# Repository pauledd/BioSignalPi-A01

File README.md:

# BioSignalPi-A01

Eagle files for the BioSignalPi-A01 egc prototype.  
For application software look at http://martinr89.github.io/BiosignalPI  

Biosignal PI is licensed by Farhad Abtahi under a Creative Commons Attribution-NonCommercial-ShareAlike 4.0 International License. You are free to:  
    
    Share — copy and redistribute the material in any medium or format
    Adapt — remix, transform, and build upon the material

The licensor cannot revoke these freedoms as long as you follow the license terms.
Under the following terms:

Attribution — You must give appropriate credit, provide a link to the license, and indicate if changes were made. You may do so in any reasonable manner, but not in any way that suggests the licensor endorses you or your use.  
What does "Attribute this work" mean?  
The page you came from contained embedded licensing metadata, including how the creator wishes to be attributed for re-use. You can use the HTML here to cite the work. Doing so will also include metadata on your page so that others can find the original work as well.  

    NonCommercial — You may not use the material for commercial purposes.

    ShareAlike — If you remix, transform, or build upon the material, you must distribute your contributions under the same license as the original.

    No additional restrictions — You may not apply legal terms or technological measures that legally restrict others from doing anything the license permits.

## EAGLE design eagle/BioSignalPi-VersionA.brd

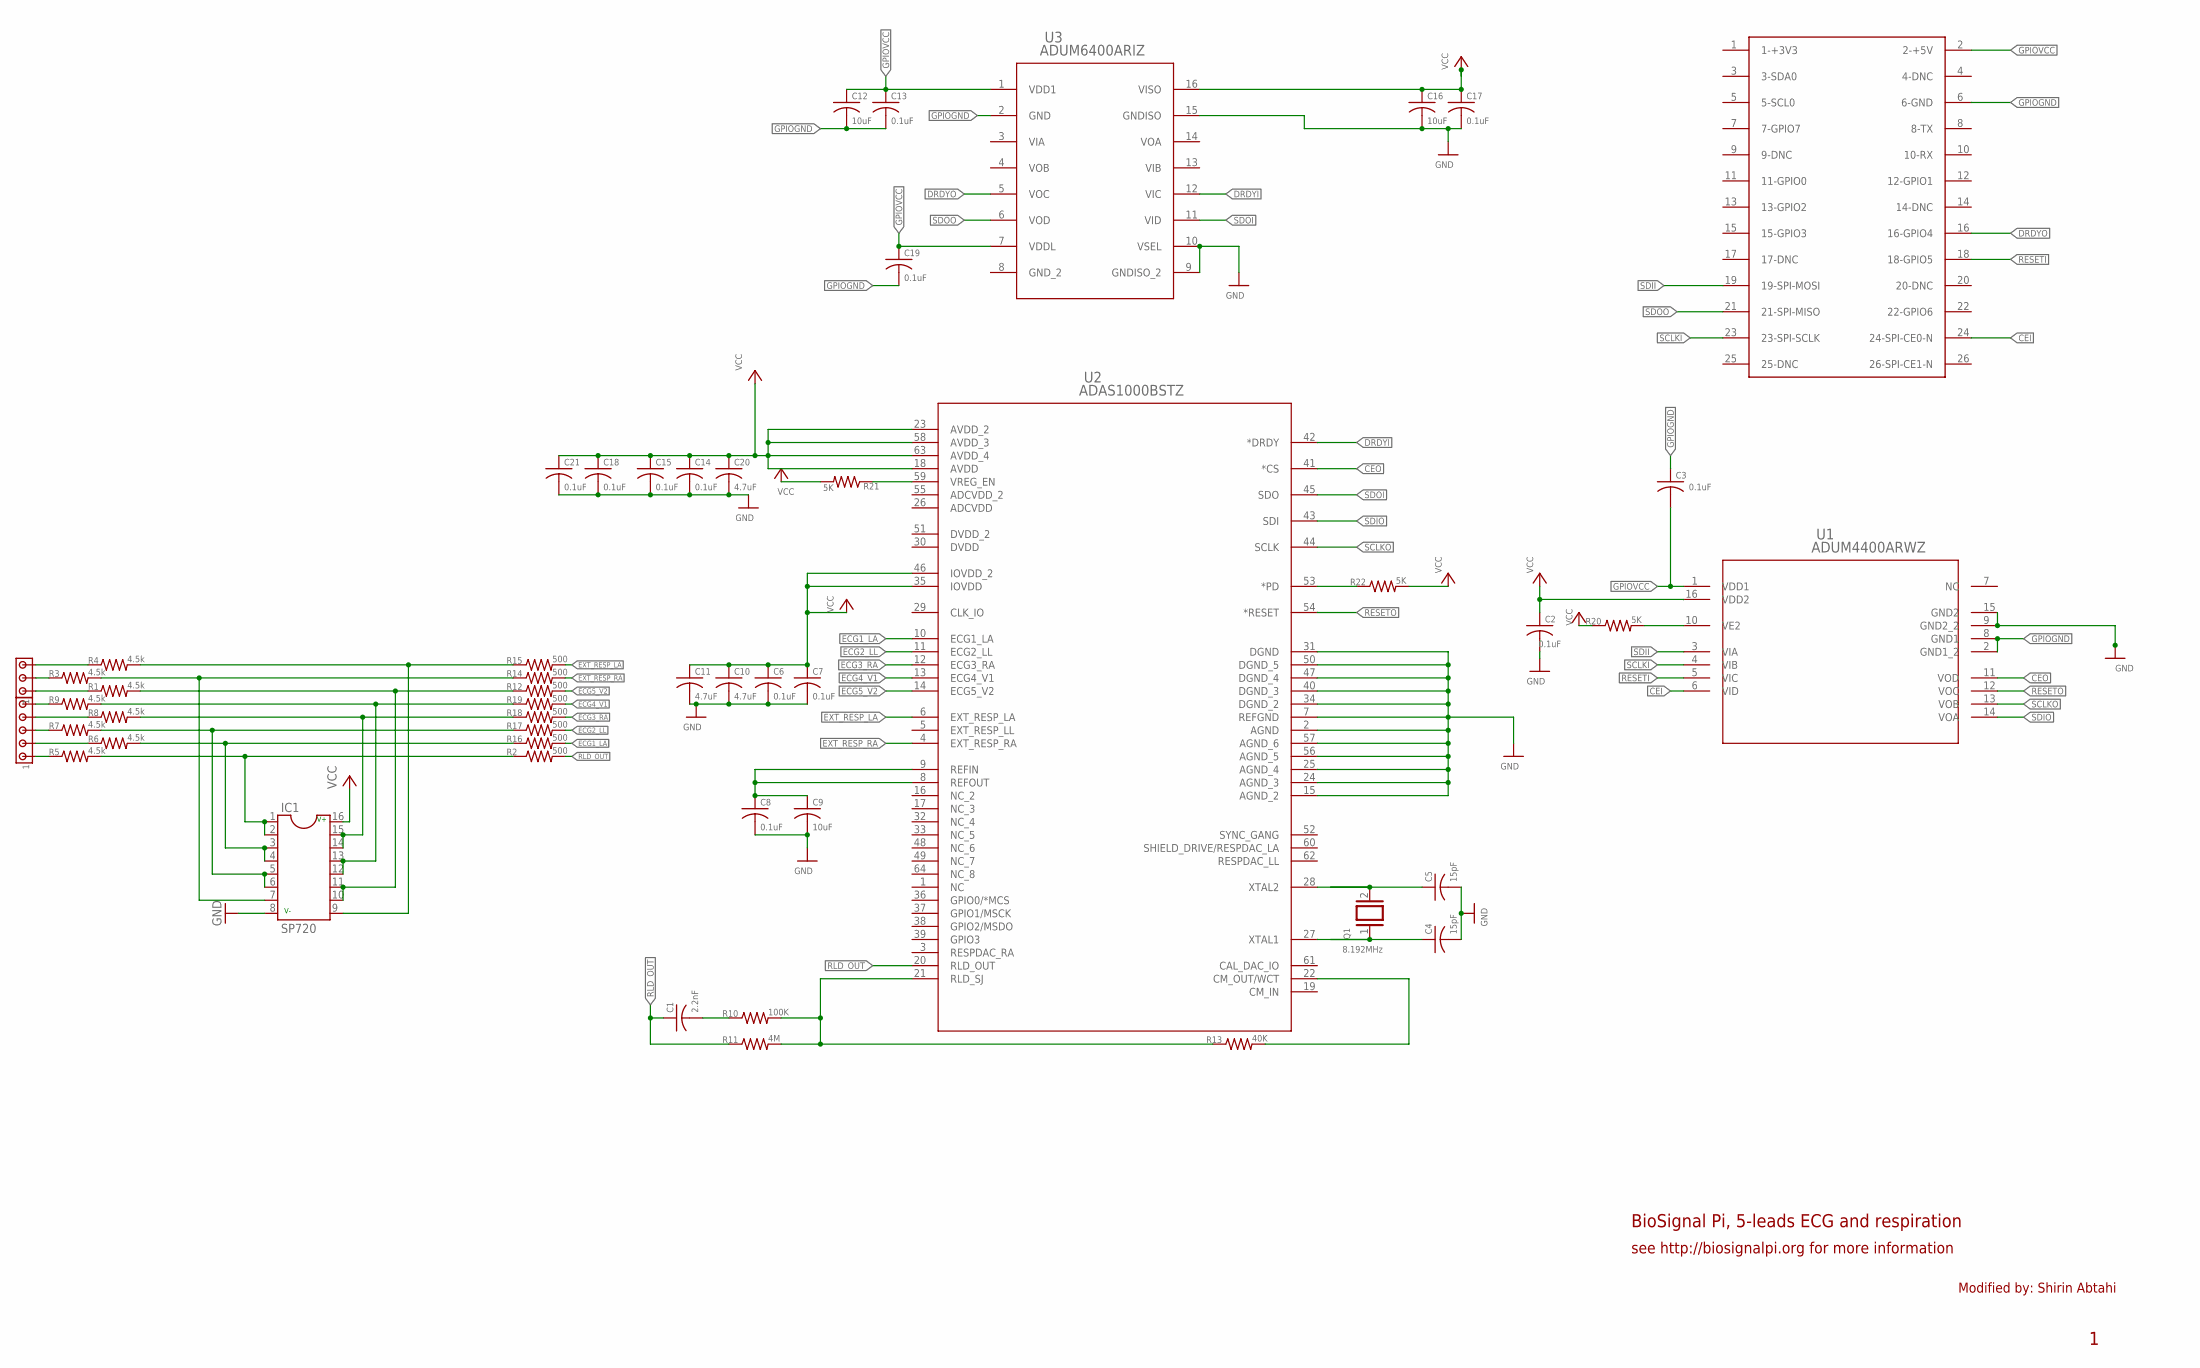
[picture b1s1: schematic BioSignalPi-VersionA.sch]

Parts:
C1: 2.2nF; C0805
C2, C3, C6, C7, C8, C13, C14, C15, C17, C18, C19, C21: 0.1uF; C0805
C4, C5: 15pF; C0805
C9, C12, C16: 10uF; C0805
C10, C11, C20: 4.7uF; C0805
IC1: SP720; DIL16
J1: JUMPERS; 10X03MTA
J2: JUMPERS; 10X05MTA
Q1: 8.192MHz; QS
R1, R3, R4, R5, R6, R7, R8, R9: 4.5k; R0805
R2, R12, R14, R15, R16, R17, R18, R19: 500; R0805
R10: 100K; R0805
R11: 4M; R0805
R13: 40K; R0805
R20, R21, R22: 5K; R0805
U1: ADUM4400ARWZ; RW_16
U2: ADAS1000BSTZ; ST_64_2
U3: ADUM6400ARIZ; RI_16_1
U$1: RASPBERRY-PI

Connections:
CEI: U1.6 (VID), U$1.24 (24-SPI-CE0-N)
CEO: U1.11 (VOD), U2.41 (*CS)
DRDYI: U2.42 (*DRDY), U3.12 (VIC)
DRDYO: U3.5 (VOC), U$1.16 (16-GPIO4)
ECG1_LA: R16.2, U2.10 (ECG1_LA)
ECG2_LL: R17.2, U2.11 (ECG2_LL)
ECG3_RA: R18.2, U2.12 (ECG3_RA)
ECG4_V1: R19.2, U2.13 (ECG4_V1)
ECG5_V2: R12.2, U2.14 (ECG5_V2)
EXT_RESP_LA: R15.2, U2.6 (EXT_RESP_LA)
EXT_RESP_RA: R14.2, U2.4 (EXT_RESP_RA)
GND: C2.2, C4.2, C5.2, C6.2, C7.2, C8.2, C9.2, C10.2, C11.2, C14.2, C15.2, C16.2, C17.2, C18.2, C20.2, C21.2, IC1.8, U1.9 (GND2_2), U1.15 (GND2), U2.2 (AGND), U2.7 (REFGND), U2.15 (AGND_2), U2.24 (AGND_3), U2.25 (AGND_4), U2.31 (DGND), U2.34 (DGND_2), U2.40 (DGND_3), U2.47 (DGND_4), U2.50 (DGND_5), U2.56 (AGND_5), U2.57 (AGND_6), U3.9 (GNDISO_2), U3.10 (VSEL), U3.15 (GNDISO)
GPIOGND: C3.1, C12.2, C13.2, C19.2, U1.2 (GND1_2), U1.8 (GND1), U3.2 (GND), U$1.6 (6-GND)
GPIOVCC: C3.2, C12.1, C13.1, C19.1, U1.1 (VDD1), U3.1 (VDD1), U3.7 (VDDL), U$1.2 (2-+5V)
JUMPERS: J1.1, R1.1
unnamed: J2.1, R5.1
unnamed: J2.2, R6.1
unnamed: J2.3, R7.1
unnamed: J2.4, R8.1
unnamed: J2.5, R9.1
unnamed: J1.2, R3.1
unnamed: J1.3, R4.1
unnamed: IC1.9, R4.2, R15.1
unnamed: IC1.7, R3.2, R14.1
unnamed: C5.1, Q1.2, U2.28 (XTAL2)
unnamed: C4.1, Q1.1, U2.27 (XTAL1)
unnamed: R10.2, R11.2, R13.1, U2.21 (RLD_SJ)
unnamed: IC1.1, IC1.2, R2.1, R5.2
unnamed: IC1.14, IC1.15, R8.2, R18.1
unnamed: IC1.12, IC1.13, R9.2, R19.1
unnamed: IC1.3, IC1.4, R6.2, R16.1
unnamed: IC1.5, IC1.6, R7.2, R17.1
unnamed: IC1.10, IC1.11, R1.2, R12.1
unnamed: R20.2, U1.10 (VE2)
unnamed: R22.1, U2.53 (*PD)
unnamed: R13.2, U2.22 (CM_OUT/WCT)
unnamed: C1.2, R10.1
unnamed: R21.1, U2.59 (VREG_EN)
unnamed: C8.1, C9.1, U2.8 (REFOUT), U2.9 (REFIN)
RESETI: U1.5 (VIC), U$1.18 (18-GPIO5)
RESETO: U1.12 (VOC), U2.54 (*RESET)
RLD_OUT: C1.1, R2.2, R11.1, U2.20 (RLD_OUT)
SCLKI: U1.4 (VIB), U$1.23 (23-SPI-SCLK)
SCLKO: U1.13 (VOB), U2.44 (SCLK)
SDII: U1.3 (VIA), U$1.19 (19-SPI-MOSI)
SDIO: U1.14 (VOA), U2.43 (SDI)
SDOI: U2.45 (SDO), U3.11 (VID)
SDOO: U3.6 (VOD), U$1.21 (21-SPI-MISO)
VCC: C2.1, C6.1, C7.1, C10.1, C11.1, C14.1, C15.1, C16.1, C17.1, C18.1, C20.1, C21.1, IC1.16, R20.1, R21.2, R22.2, U1.16 (VDD2), U2.18 (AVDD), U2.23 (AVDD_2), U2.35 (IOVDD), U2.46 (IOVDD_2), U2.58 (AVDD_3), U2.63 (AVDD_4), U3.16 (VISO)

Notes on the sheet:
BioSignal Pi, 5-leads ECG and respiration
see http://biosignalpi.org for more information
Modified by: Shirin Abtahi

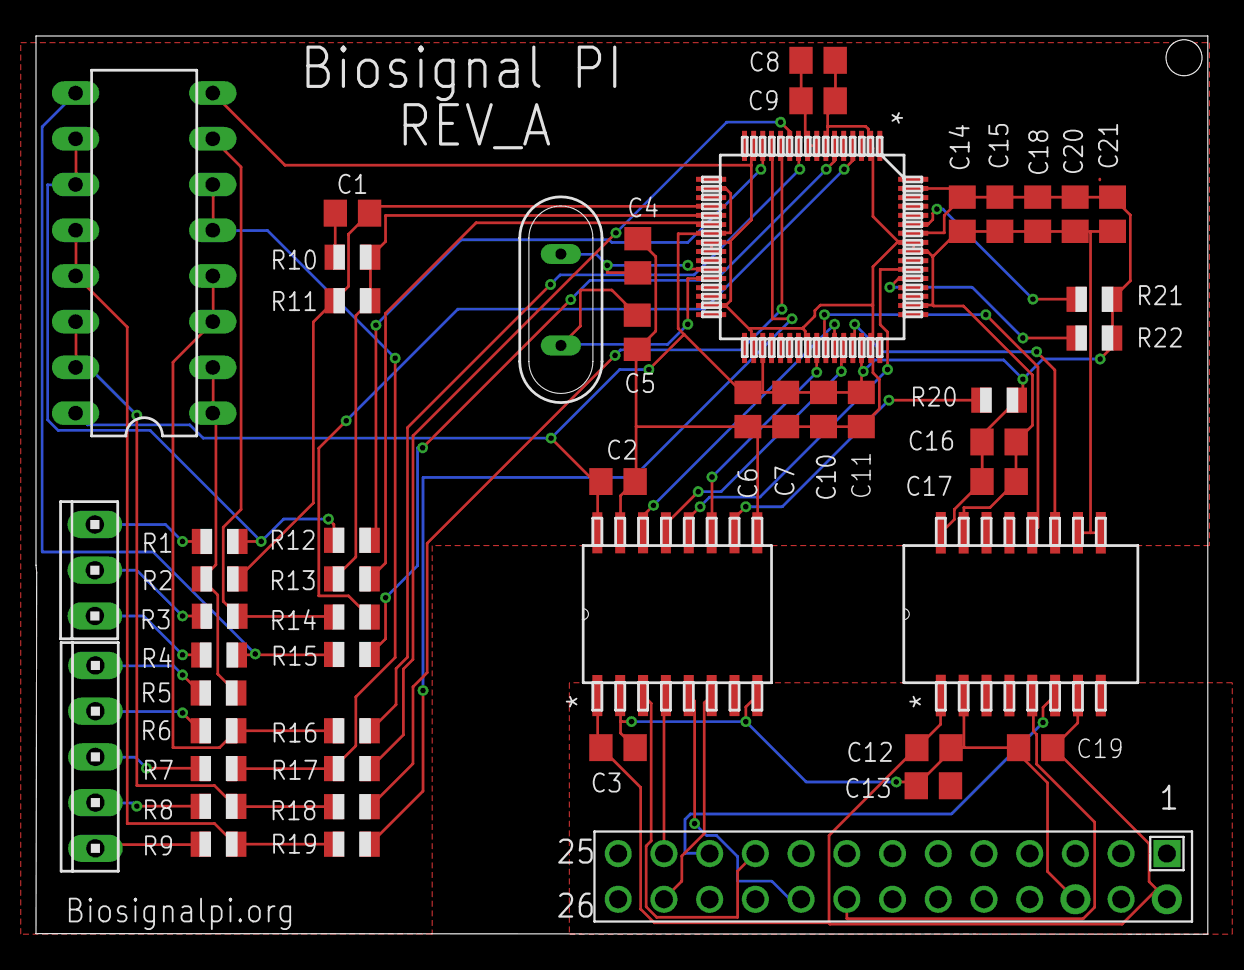
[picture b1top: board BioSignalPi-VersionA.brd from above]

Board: 2 copper layers, 65.1 x 49.9 mm, 51 parts (0 on the bottom side), 49 nets.

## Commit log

2019-08-13 Readme added
2019-08-13 ncsa added
2019-08-13 eagle files added
2019-08-13 pdf files added
2019-08-13 text changed
